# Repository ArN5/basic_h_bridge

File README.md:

# basic_h_bridge
This is a basic H bridge PCB for educational purposes and teaching.
MOSFET that will be used are the IRF5305

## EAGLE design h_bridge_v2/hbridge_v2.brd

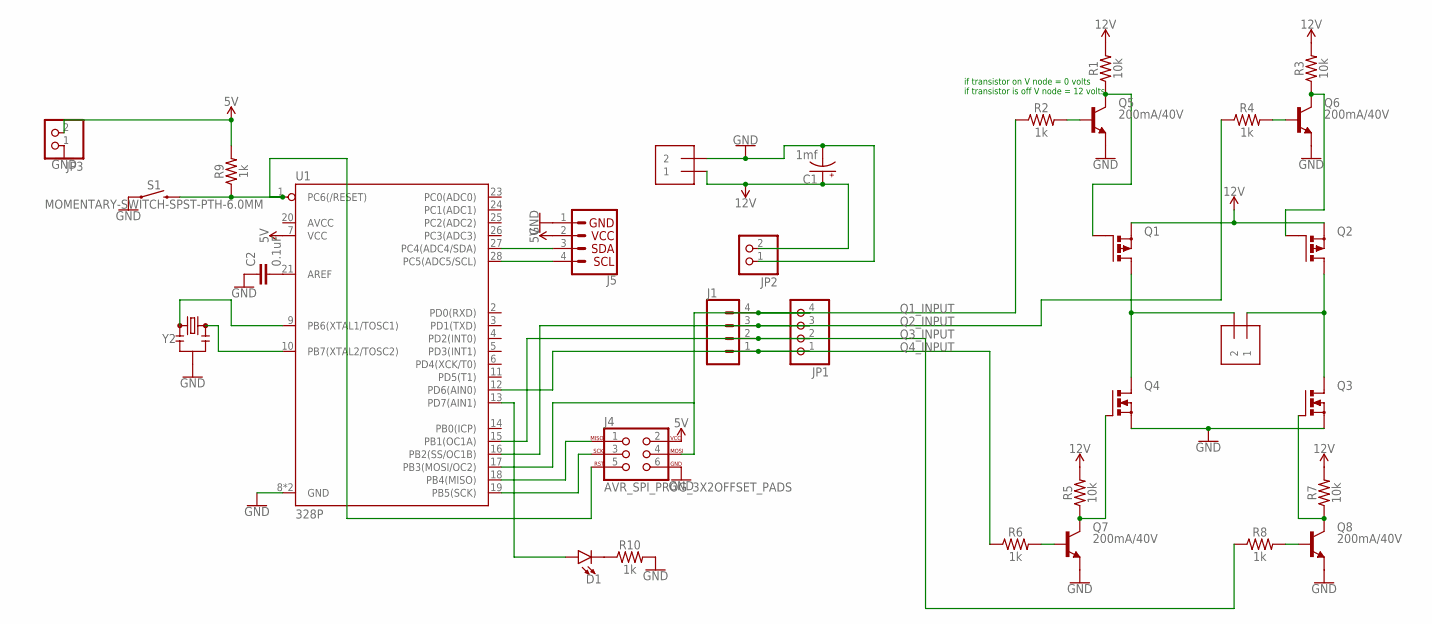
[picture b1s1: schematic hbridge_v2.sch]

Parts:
C1: 1mf; CPOL-RADIAL-5MM-10MM-KIT
C2: 0.1uF; CAP-PTH-SMALL-KIT
D1: LED3MM; LED_3MM
J1: CONN_04LONGPADS; 1X04_LONGPADS
J2, J3: 1X2-3.5MM
J4: AVR_SPI_PROG_3X2OFFSET_PADS; 2X3_OFFSET
J5: I2C_STANDARD; 1X04
JP1: PINHD-1X4; 1X04
JP2, JP3: PINHD-1X2; 1X02
Q1, Q2: PMOSFET_PTO220BV; TO220BV
Q3, Q4: PMOSFET_NTO220BV; TO220BV
Q5, Q6, Q7, Q8: 200mA/40V; TO-92
R1, R3, R5, R7: 10k; AXIAL-0.3
R2, R4, R6, R8, R9, R10: 1k; AXIAL-0.3
S1: MOMENTARY-SWITCH-SPST-PTH-6.0MM; TACTILE_SWITCH_PTH_6.0MM
U1: 328P; DIP28
Y2: RESONATORPTH-7.6X3.8; RESONATOR-PTH-7.6X3.8

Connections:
5V: J4.2, J5.2, JP3.2, R9.P$2 (2), U1.7 (VCC)
12V: C1.+, J3.1, JP2.2, Q1.S, Q2.S, R1.P$2 (2), R3.P$2 (2), R5.P$2 (2), R7.P$2 (2)
GND: C1.-, C2.1, J3.2, J4.6, J5.1, JP2.1, JP3.1, Q3.S, Q4.S, Q5.1 (E), Q6.1 (E), Q7.1 (E), Q8.1 (E), R10.P$2 (2), S1.1, U1.8 (GND), U1.22 (GND), Y2.2
unnamed: J2.1, Q2.D, Q3.D
unnamed: J2.2, Q1.D, Q4.D
unnamed: Q5.2 (B), R2.P$2 (2)
unnamed: U1.10 (PB7(XTAL2/TOSC2)), Y2.3
unnamed: U1.9 (PB6(XTAL1/TOSC1)), Y2.1
unnamed: Q1.G, Q5.3 (C), R1.P$1 (1)
unnamed: J4.5, R9.P$1 (1), S1.3 (2), U1.1 (PC6(/RESET))
unnamed: Q2.G, Q6.3 (C), R3.P$1 (1)
unnamed: Q6.2 (B), R4.P$2 (2)
unnamed: Q4.G, Q7.3 (C), R5.P$1 (1)
unnamed: Q7.2 (B), R6.P$2 (2)
unnamed: Q3.G, Q8.3 (C), R7.P$1 (1)
unnamed: Q8.2 (B), R8.P$2 (2)
unnamed: C2.2, U1.21 (AREF)
unnamed: J4.1, U1.18 (PB4(MISO))
unnamed: J4.3, U1.19 (PB5(SCK))
unnamed: D1.A, U1.13 (PD7(AIN1))
unnamed: D1.K (C), R10.P$1 (1)
unnamed: J5.3, U1.27 (PC4(ADC4/SDA))
unnamed: J5.4, U1.28 (PC5(ADC5/SCL))
Q1_INPUT: J1.4, J4.4, JP1.4, R2.P$1 (1), U1.17 (PB3(MOSI/OC2))
Q2_INPUT: J1.3, JP1.3, R4.P$1 (1), U1.16 (PB2(SS/OC1B))
Q3_INPUT: J1.2, JP1.2, R8.P$1 (1), U1.15 (PB1(OC1A))
Q4_INPUT: J1.1, JP1.1, R6.P$1 (1), U1.12 (PD6(AIN0))

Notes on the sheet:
if transistor on V node = 0 volts if transistor is off V node = 12 volts

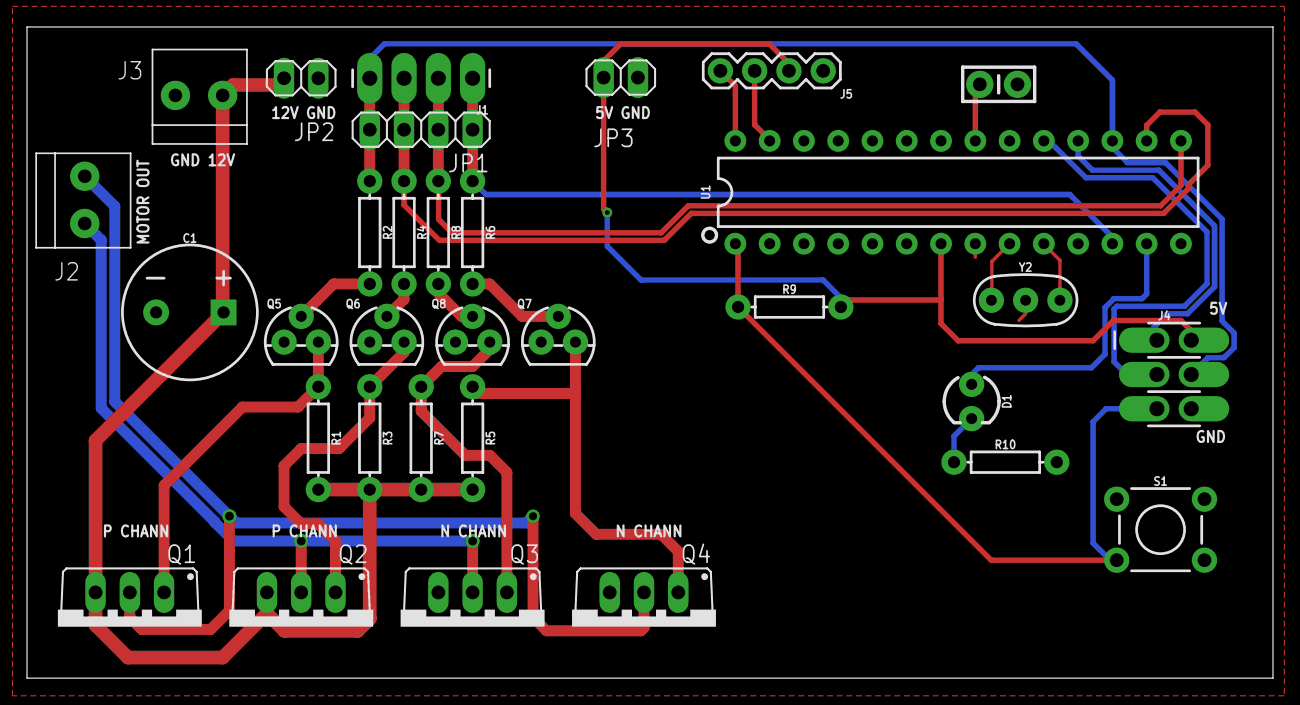
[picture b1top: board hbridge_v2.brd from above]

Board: 2 copper layers, 92.3 x 48.2 mm, 32 parts (0 on the bottom side), 27 nets.

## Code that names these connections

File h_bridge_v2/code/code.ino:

//PB1=9, PB2=10, PB3=11, PD6=6
#define MOTOR_PIN1 9 //n channel? p channel
#define MOTOR_PIN2 10
#define MOTOR_PIN3 11
#define MOTOR_PIN4 6

void setup() {
  // put your setup code here, to run once:

  //we will use all 4 pins as outputs 
  //to control the h bridge
  pinMode(MOTOR_PIN1, OUTPUT);
  pinMode(MOTOR_PIN2, OUTPUT);
  pinMode(MOTOR_PIN3, OUTPUT);
  pinMode(MOTOR_PIN4, OUTPUT);

  digitalWrite(MOTOR_PIN1,LOW);//0v is low
  digitalWrite(MOTOR_PIN2,LOW);
  digitalWrite(MOTOR_PIN3,LOW);
  digitalWrite(MOTOR_PIN4,LOW);
  
}

void loop() {
  // put your main code here, to run repeatedly:

}

void clockwise(){
  digitalWrite(MOTOR_PIN1,LOW);//0v is low
  digitalWrite(MOTOR_PIN2,LOW);
  digitalWrite(MOTOR_PIN3,HIGH);
  digitalWrite(MOTOR_PIN4,LOW);
}

void counter_clockwise(){
  digitalWrite(MOTOR_PIN1,HIGH);//0v is low
  digitalWrite(MOTOR_PIN2,LOW);
  digitalWrite(MOTOR_PIN3,LOW);
  digitalWrite(MOTOR_PIN4,LOW);
}

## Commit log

2020-07-16 Added the PCB files
    added brd file and the sch file.
2020-07-16 added image of the board layout
2020-07-16 created a folder for the v1 board
2020-07-16 created the v2 board
    motor controller now has a microntroller
2020-07-16 updated README.md with MOSFETS
2020-07-16 attempted to route
2020-07-16 replaced the resonator with through hole one
2020-07-24 added connections to PWM pins
2020-07-25 added I2C port and some topnames
2020-08-20 added more leds
2020-08-27 adding basic program

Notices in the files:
parts and their libraries:
SparkFun-Capacitors: Licensing: Creative Commons ShareAlike 4.0 International - https://creativecommons.org/licenses/by-sa/4.0
